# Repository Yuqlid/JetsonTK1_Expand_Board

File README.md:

# JetsonTK1_Expand_Board
2016年12月31日　コミックマーケット91(C91)3日目(Sat)にて頒布した基板のCADデータです．  
設計に使用したCADは[Kicad](http://kicad-pcb.org/)(4.0.4)です．

# 作り方
組立方法は[Wiki](https://github.com/Yuqlid/JetsonTK1_Expand_Board/wiki)を参照してください．

# LICENSE
See LICENSE

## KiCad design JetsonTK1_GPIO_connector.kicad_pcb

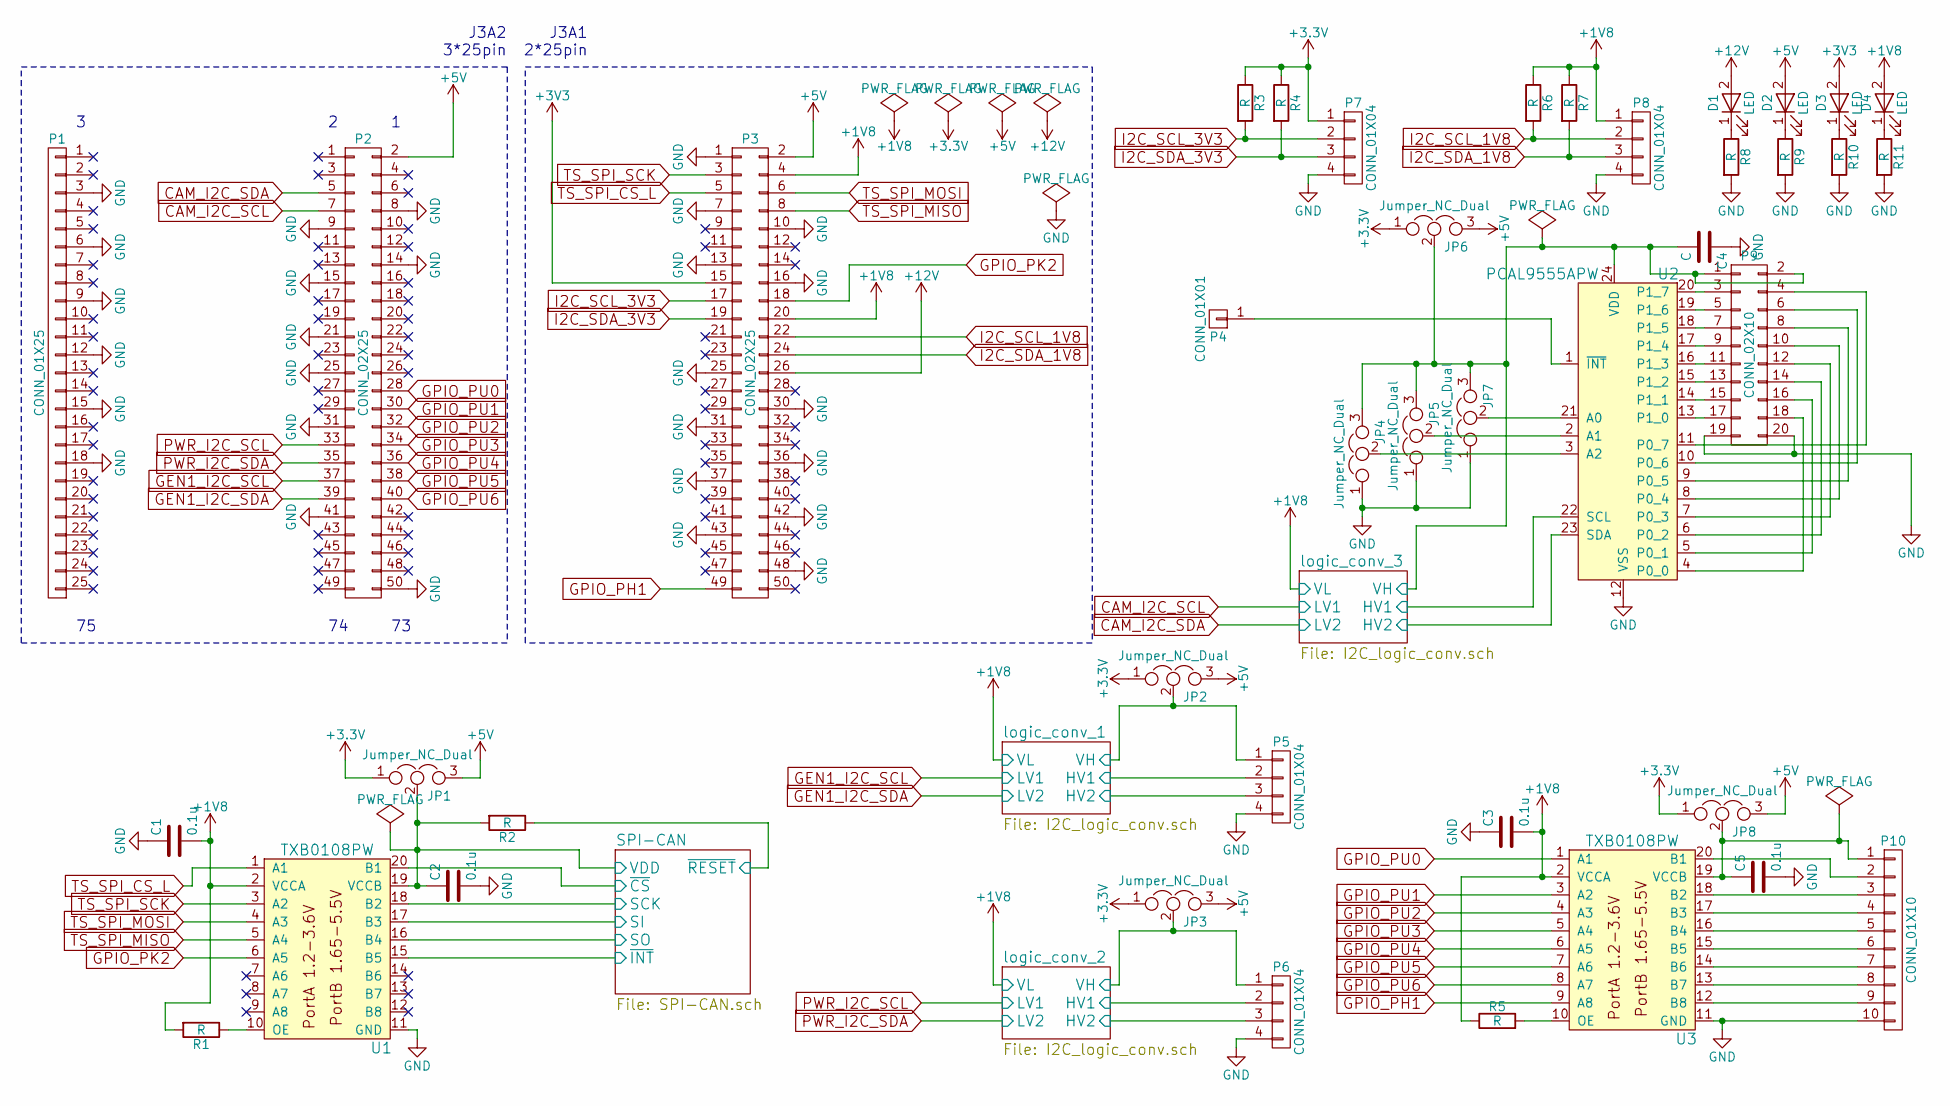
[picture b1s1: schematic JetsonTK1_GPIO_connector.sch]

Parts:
C1, C2, C3, C5: 0.1u; C_0603
C4: C; C_0603
D1, D2, D3, D4: LED; LED_0603
JP1, JP2, JP3, JP4, JP5, JP6, JP7, JP8: Jumper_NC_Dual; GS3
P1: CONN_01X25; Pin_Header_Straight_1x25_Pitch2.00mm
P2, P3: CONN_02X25; Pin_Header_Straight_2x25_Pitch2.00mm
P4: CONN_01X01; Pin_Header_Straight_1x01
P5, P6, P7, P8: CONN_01X04; JST_XH_B04B-XH-A_04x2.50mm_Straight
P9: CONN_02X10; Multicomp_MC9A12-2034_2x10x2.54mm_Straight
P10: CONN_01X10; JST_XH_B10B-XH-A_10x2.50mm_Straight
R1, R2, R3, R4, R5, R6, R7, R8, R9, R10, R11: R; R_0603
U1, U3: TXB0108PW; TSSOP-20_4.4x6.5mm_Pitch0.65mm
U2: PCAL9555APW; TSSOP-24_4.4x7.8mm_Pitch0.65mm

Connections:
+1V8: C1.2, C3.2, D4.2 (A), P3.4, P3.20, P8.1, R1.2, R5.1, R6.1, R7.1, U1.2 (VCCA), U3.2 (VCCA); also elsewhere on the board
+5V: D2.2 (A), JP1.3, JP2.3, JP3.3, JP6.3, JP8.3, P2.2, P3.2; also elsewhere on the board
+12V: D1.2 (A), P3.26
/SPI-CAN/SCK: U1.18 (B2); also elsewhere on the board
/SPI-CAN/SI: U1.17 (B3); also elsewhere on the board
/SPI-CAN/SO: U1.16 (B4); also elsewhere on the board
/SPI-CAN/VDD: C2.1, JP1.2, R2.2, U1.19 (VCCB); also elsewhere on the board
/SPI-CAN/~CS: U1.20 (B1); also elsewhere on the board
/SPI-CAN/~INT: U1.15 (B5); also elsewhere on the board
/SPI-CAN/~RESET: R2.1; also elsewhere on the board
/logic_conv_1/HV1: P5.2; also elsewhere on the board
/logic_conv_1/HV2: P5.3; also elsewhere on the board
/logic_conv_1/VH: JP2.2, P5.1; also elsewhere on the board
/logic_conv_2/HV1: P6.2; also elsewhere on the board
/logic_conv_2/HV2: P6.3; also elsewhere on the board
/logic_conv_2/VH: JP3.2, P6.1; also elsewhere on the board
/logic_conv_3/HV1: U2.22 (SCL); also elsewhere on the board
/logic_conv_3/HV2: U2.23 (SDA); also elsewhere on the board
/logic_conv_3/VH: C4.2, JP4.3, JP5.3, JP6.2, JP7.3, P9.1, P9.2, U2.24 (VDD); also elsewhere on the board
CAM_I2C_SCL: P2.7; also elsewhere on the board
CAM_I2C_SDA: P2.5; also elsewhere on the board
GEN1_I2C_SCL: P2.37; also elsewhere on the board
GEN1_I2C_SDA: P2.39; also elsewhere on the board
GND: C1.1, C2.2, C3.1, C4.1, C5.2, JP4.1, JP5.1, JP7.1, P1.3, P1.6, P1.9, P1.12, P1.15, P1.18, P2.8, P2.9, P2.14, P2.15, P2.21, P2.25, P2.31, P2.41, P2.50, P3.1, P3.7, P3.10, P3.13, P3.16, P3.25, P3.30, P3.31, P3.36, P3.37, P3.42, P3.43, P3.48, P5.4, P6.4, P7.4, P8.4, P9.19, P9.20, P10.10, R8.2, R9.2, R10.2, R11.2, U1.11 (GND), U2.12 (VSS), U3.11 (GND); also elsewhere on the board
GPIO_PH1: P3.49, U3.9 (A8)
GPIO_PK2: P3.18, U1.6 (A5)
GPIO_PU0: P2.28, U3.1 (A1)
GPIO_PU1: P2.30, U3.3 (A2)
GPIO_PU2: P2.32, U3.4 (A3)
GPIO_PU3: P2.34, U3.5 (A4)
GPIO_PU4: P2.36, U3.6 (A5)
GPIO_PU5: P2.38, U3.7 (A6)
GPIO_PU6: P2.40, U3.8 (A7)
I2C_SCL_1V8: P3.22, P8.2, R6.2
I2C_SCL_3V3: P3.17, P7.2, R3.2
I2C_SDA_1V8: P3.24, P8.3, R7.2
I2C_SDA_3V3: P3.19, P7.3, R4.2
unnamed: C5.1, JP8.2, P10.1, U3.19 (VCCB)
unnamed: D1.1 (K), R8.1
unnamed: D2.1 (K), R9.1
unnamed: D3.1 (K), R10.1
unnamed: D4.1 (K), R11.1
unnamed: JP4.2, U2.3 (A2)
unnamed: JP5.2, U2.2 (A1)
unnamed: JP7.2, U2.21 (A0)
unnamed: P4.1, U2.1 (~INT)
unnamed: P9.3, U2.20 (P1_7)
unnamed: P9.4, U2.11 (P0_7)
unnamed: P9.5, U2.19 (P1_6)
unnamed: P9.6, U2.10 (P0_6)
unnamed: P9.7, U2.18 (P1_5)
unnamed: P9.8, U2.9 (P0_5)
unnamed: P9.9, U2.17 (P1_4)
unnamed: P9.10, U2.8 (P0_4)
unnamed: P9.11, U2.16 (P1_3)
unnamed: P9.12, U2.7 (P0_3)
unnamed: P9.13, U2.15 (P1_2)
unnamed: P9.14, U2.6 (P0_2)
unnamed: P9.15, U2.14 (P1_1)
unnamed: P9.16, U2.5 (P0_1)
unnamed: P9.17, U2.13 (P1_0)
unnamed: P9.18, U2.4 (P0_0)
unnamed: P10.2, U3.20 (B1)
unnamed: P10.3, U3.18 (B2)
unnamed: P10.4, U3.17 (B3)
unnamed: P10.5, U3.16 (B4)
unnamed: P10.6, U3.15 (B5)
unnamed: P10.7, U3.14 (B6)
unnamed: P10.8, U3.13 (B7)
unnamed: P10.9, U3.12 (B8)
unnamed: R1.1, U1.10 (OE)
unnamed: R5.2, U3.10 (OE)
PWR_I2C_SCL: P2.33; also elsewhere on the board
PWR_I2C_SDA: P2.35; also elsewhere on the board
TS_SPI_CS_L: P3.5, U1.1 (A1)
TS_SPI_MISO: P3.8, U1.5 (A4)
TS_SPI_MOSI: P3.6, U1.4 (A3)
TS_SPI_SCK: P3.3, U1.3 (A2)

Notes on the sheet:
J3A1 2*25pin
J3A2 3*25pin

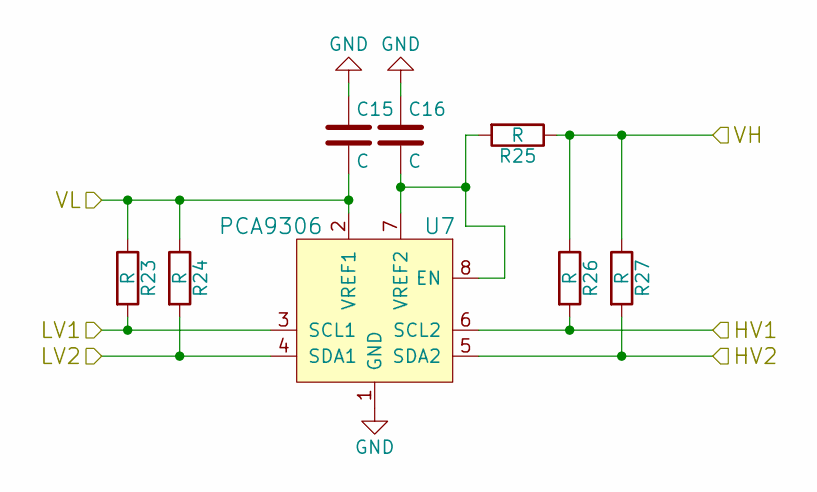
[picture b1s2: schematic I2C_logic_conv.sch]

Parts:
C6, C7: C; C_0603
R12, R13, R14, R15, R16: R; R_0603
U4: PCA9306; MSOP-8_3x3mm_Pitch0.65mm

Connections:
+1V8: C6.2, R12.1, R13.1, U4.2 (VREF1); also elsewhere on the board
/logic_conv_1/HV1: R15.2, U4.6 (SCL2); also elsewhere on the board
/logic_conv_1/HV2: R16.2, U4.5 (SDA2); also elsewhere on the board
/logic_conv_1/VH: R14.1, R15.1, R16.1; also elsewhere on the board
GEN1_I2C_SCL: R12.2, U4.3 (SCL1); also elsewhere on the board
GEN1_I2C_SDA: R13.2, U4.4 (SDA1); also elsewhere on the board
GND: C6.1, C7.1, U4.1 (GND); also elsewhere on the board
unnamed: C7.2, R14.2, U4.7 (VREF2), U4.8 (EN)

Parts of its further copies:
C8, C9, C15, C16: C; C_0603
R17, R18, R19, R20, R21, R23, R24, R25, R26, R27: R; R_0603
U5, U7: PCA9306; MSOP-8_3x3mm_Pitch0.65mm

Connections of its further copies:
+1V8: C8.2, C15.2, R17.1, R18.1, R23.1, R24.1, U5.2 (VREF1), U7.2 (VREF1); also elsewhere on the board
/logic_conv_2/HV1: R20.2, U5.6 (SCL2); also elsewhere on the board
/logic_conv_2/HV2: R21.2, U5.5 (SDA2); also elsewhere on the board
/logic_conv_2/VH: R19.1, R20.1, R21.1; also elsewhere on the board
/logic_conv_3/HV1: R26.2, U7.6 (SCL2); also elsewhere on the board
/logic_conv_3/HV2: R27.2, U7.5 (SDA2); also elsewhere on the board
/logic_conv_3/VH: R25.1, R26.1, R27.1; also elsewhere on the board
CAM_I2C_SCL: R23.2, U7.3 (SCL1); also elsewhere on the board
CAM_I2C_SDA: R24.2, U7.4 (SDA1); also elsewhere on the board
GND: C8.1, C9.1, C15.1, C16.1, U5.1 (GND), U7.1 (GND); also elsewhere on the board
unnamed: C9.2, R19.2, U5.7 (VREF2), U5.8 (EN)
unnamed: C16.2, R25.2, U7.7 (VREF2), U7.8 (EN)
PWR_I2C_SCL: R17.2, U5.3 (SCL1); also elsewhere on the board
PWR_I2C_SDA: R18.2, U5.4 (SDA1); also elsewhere on the board

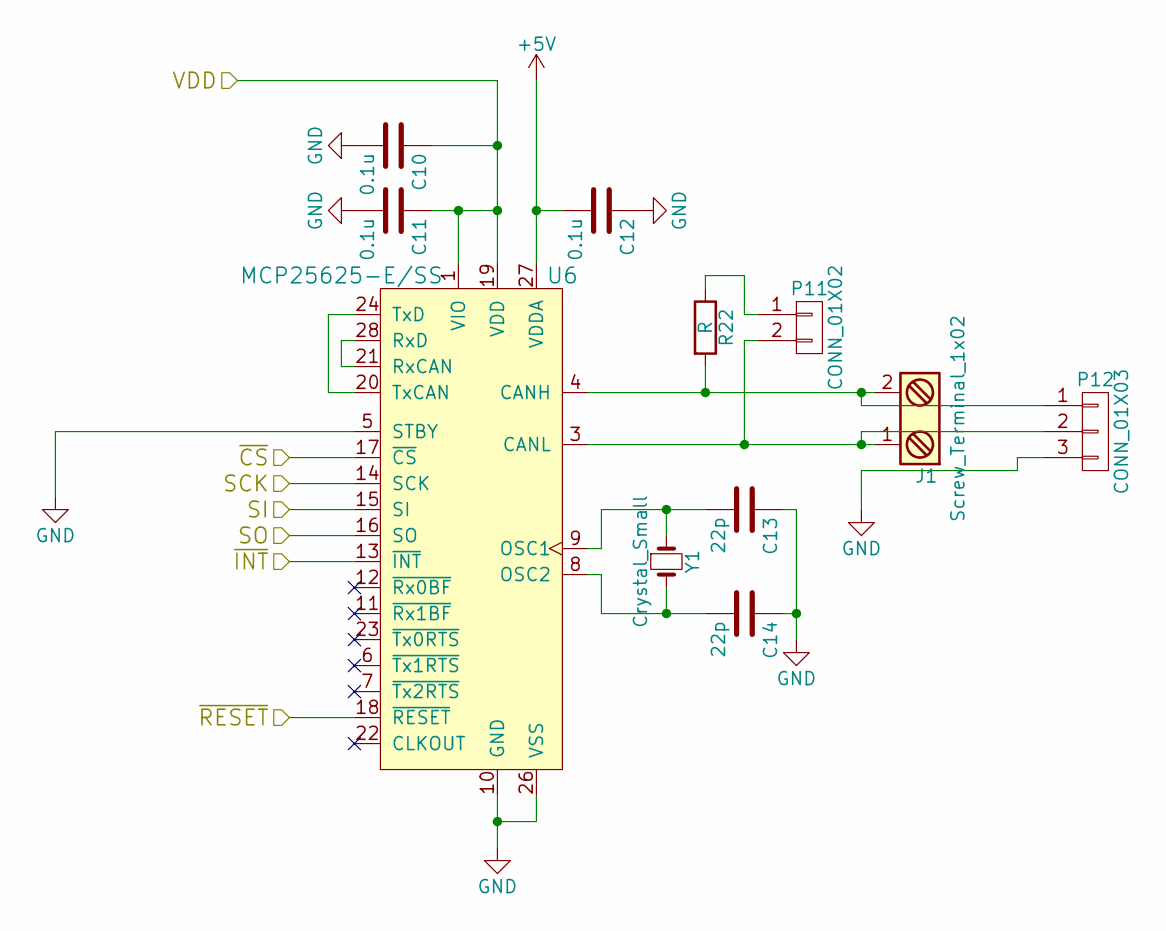
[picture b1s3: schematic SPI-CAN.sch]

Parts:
C10, C11, C12: 0.1u; C_0603
C13, C14: 22p; C_0603
J1: Screw_Terminal_1x02; TerminalBlock_Pheonix_MKDS1.5-2pol
P11: CONN_01X02; Pin_Header_Straight_1x02
P12: CONN_01X03; Pin_Header_Straight_1x03
R22: R; R_0603
U6: MCP25625-E/SS; SSOP-28_5.3x10.2mm_Pitch0.65mm
Y1: Crystal_Small; Crystal_HC49-U_Vertical

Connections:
+5V: C12.2, U6.27 (VDDA); also elsewhere on the board
/SPI-CAN/SCK: U6.14 (SCK); also elsewhere on the board
/SPI-CAN/SI: U6.15 (SI); also elsewhere on the board
/SPI-CAN/SO: U6.16 (SO); also elsewhere on the board
/SPI-CAN/VDD: C10.1, C11.1, U6.1 (VIO), U6.19 (VDD); also elsewhere on the board
/SPI-CAN/~CS: U6.17 (~CS); also elsewhere on the board
/SPI-CAN/~INT: U6.13 (~INT); also elsewhere on the board
/SPI-CAN/~RESET: U6.18 (~RESET); also elsewhere on the board
GND: C10.2, C11.2, C12.1, C13.1, C14.1, P12.3, U6.5 (STBY), U6.10 (GND), U6.26 (VSS); also elsewhere on the board
unnamed: C13.2, U6.9 (OSC1), Y1.1
unnamed: C14.2, U6.8 (OSC2), Y1.2
unnamed: J1.1, P11.2, P12.2, U6.3 (CANL)
unnamed: J1.2, P12.1, R22.2, U6.4 (CANH)
unnamed: P11.1, R22.1
unnamed: U6.20 (TxCAN), U6.24 (TxD)
unnamed: U6.21 (RxCAN), U6.28 (RxD)

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
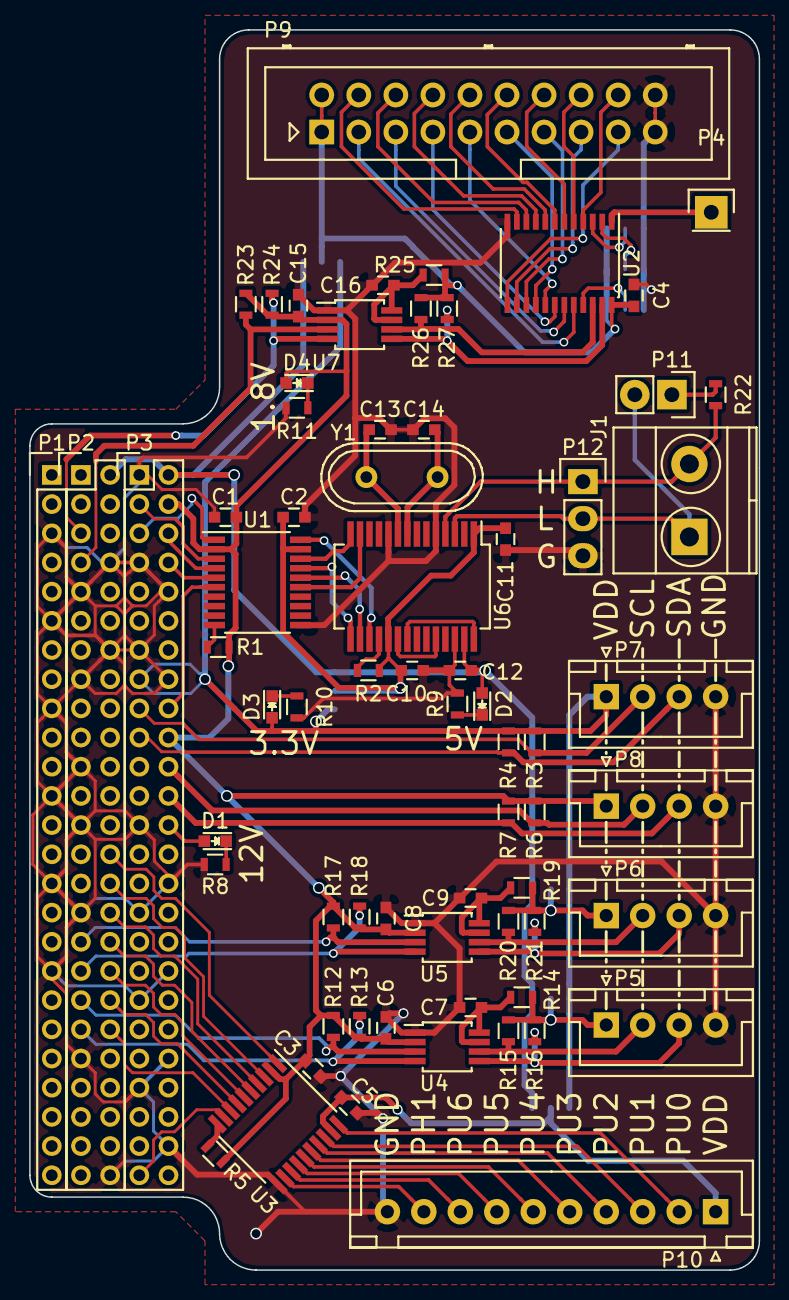
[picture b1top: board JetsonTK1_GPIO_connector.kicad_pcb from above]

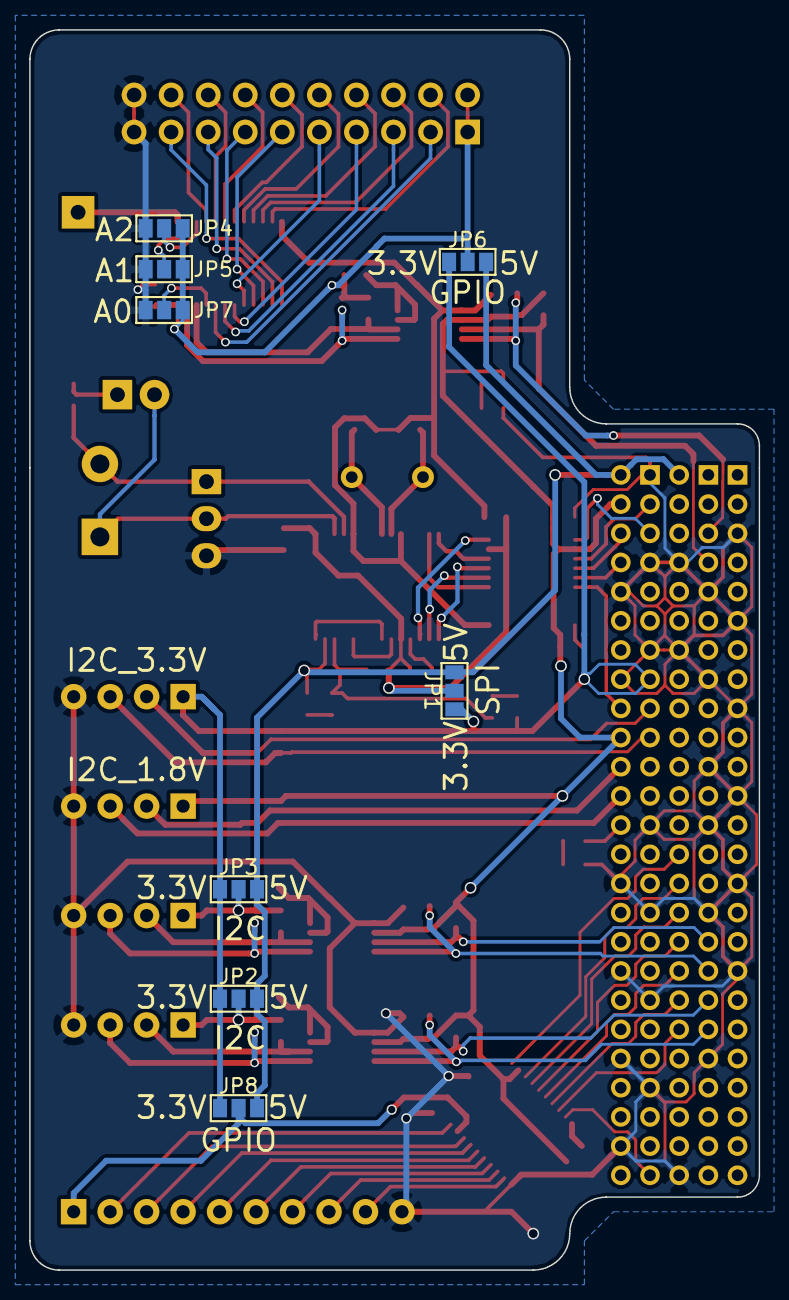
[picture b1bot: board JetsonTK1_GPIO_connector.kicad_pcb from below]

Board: 2 copper layers, 50.0 x 85.0 mm, 76 parts (8 on the bottom side), 89 nets.

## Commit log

2016-11-02 GPIOとi2cを追加
2016-11-25 シート追加
2016-11-26 IC追加
2016-11-26 アートワーク編集
2016-11-27 アートワーク開始
2016-11-30 LED以外接続完了
2016-11-30 ver1.0完成，これでElecrow発注
2016-12-18 図面にタイトルを追加
2016-12-18 名称変更，再アノテーション
2016-12-18 via追加
2016-12-18 コミックマーケット91用基板ガーバ出力
2016-12-29 部品に定数を追加
2016-12-30 BOMを追加
2016-12-30 Create LICENSE
2016-12-30 Set theme jekyll-theme-cayman
2017-07-01 図面をPDFに出力
